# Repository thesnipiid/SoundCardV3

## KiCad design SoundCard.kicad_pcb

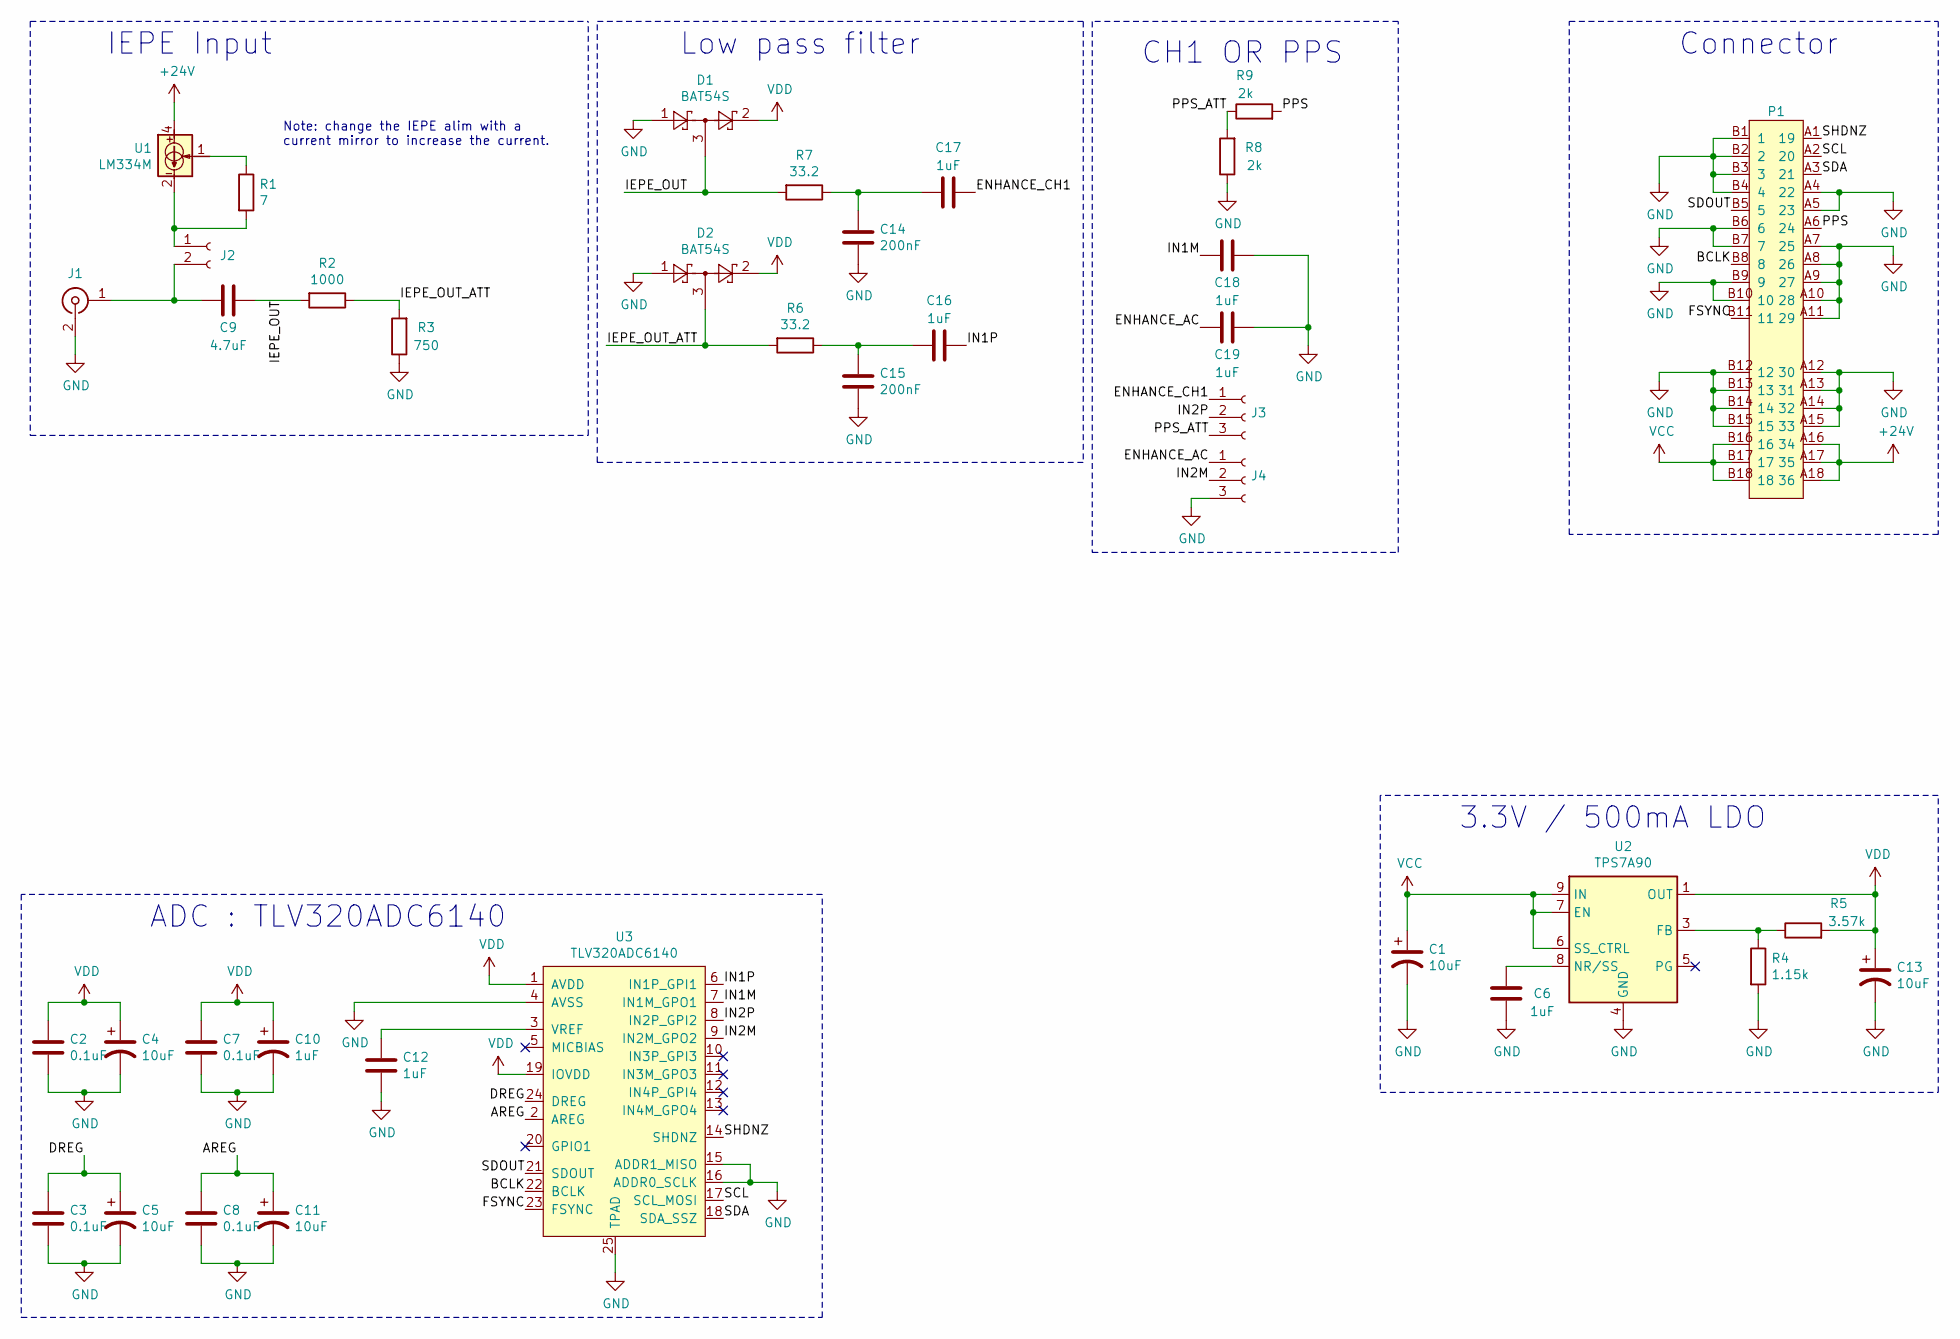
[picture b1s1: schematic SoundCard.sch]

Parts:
C1, C4, C5, C11, C13: 10uF; C_0805_2012Metric
C2, C3, C7, C8: 0.1uF; C_0402_1005Metric
C6, C12, C16, C17, C18, C19: 1uF; C_0402_1005Metric
C9: 4.7uF; C_0805_2012Metric
C10: 1uF; C_0805_2012Metric
C14, C15: 200nF; C_0402_1005Metric
D1, D2: BAT54S; SOT-23
J1: Conn_Coaxial_inv; SMA_Amphenol_901-144_Vertical
J2: Conn_01x02_Female; SolderJumper-2_P1.3mm_Bridged_Pad1.0x1.5mm
J3, J4: Conn_01x03_Female; SolderJumper-3_P1.3mm_Open_Pad1.0x1.5mm
P1: CONN_36_P1.00_PCI; BUS_PCIexpress_x1
R1: 7; R_0603_1608Metric
R2: 1000; R_0402_1005Metric
R3: 750; R_0402_1005Metric
R4: 1.15k; R_0402_1005Metric
R5: 3.57k; R_0402_1005Metric
R6, R7: 33.2; R_0402_1005Metric
R8, R9: 2k; R_0402_1005Metric
U1: LM334M; SOIC-8_3.9x4.9mm_P1.27mm
U2: TPS7A90; Texas_S-PDSO-N10_EP1.2x2mm
U3: TLV320ADC6140; Texas_S-PWQFN-N24_EP2.7x2.7mm_ThermalVias

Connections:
+24V: P1.A16 (34), P1.A17 (35), P1.A18 (36), U1.4
/AREG: C8.2, C11.1, U3.2 (AREG)
/BCLK: P1.B8 (8), U3.22 (BCLK)
/DREG: C3.2, C5.1, U3.24 (DREG)
/ENHANCE_AC: C19.1, J4.1
/ENHANCE_CH1: C17.2, J3.1
/FSYNC: P1.B11 (11), U3.23 (FSYNC)
/IEPE_OUT: C9.2, D1.3, R2.2, R7.2
/IEPE_OUT_ATT: D2.3, R2.1, R3.2, R6.2
/IN1M: C18.1, U3.7 (IN1M_GPO1)
/IN1P: C16.2, U3.6 (IN1P_GPI1)
/IN2M: J4.2, U3.9 (IN2M_GPO2)
/IN2P: J3.2, U3.8 (IN2P_GPI2)
/PPS: P1.A6 (24), R9.2
/PPS_ATT: J3.3, R8.2, R9.1
/SCL: P1.A2 (20), U3.17 (SCL_MOSI)
/SDA: P1.A3 (21), U3.18 (SDA_SSZ)
/SDOUT: P1.B5 (5), U3.21 (SDOUT)
/SHDNZ: P1.A1 (19), U3.14 (SHDNZ)
GND: C1.2, C2.1, C3.1, C4.2, C5.2, C6.1, C7.1, C8.1, C10.2, C11.2, C12.1, C13.2, C14.2, C15.2, C18.2, C19.2, D1.1, D2.1, J1.2 (In), J4.3, P1.A4 (22), P1.A5 (23), P1.A7 (25), P1.A8 (26), P1.A9 (27), P1.A10 (28), P1.A11 (29), P1.A12 (30), P1.A13 (31), P1.A14 (32), P1.A15 (33), P1.B1 (1), P1.B2 (2), P1.B3 (3), P1.B4 (4), P1.B6 (6), P1.B7 (7), P1.B9 (9), P1.B10 (10), P1.B12 (12), P1.B13 (13), P1.B14 (14), P1.B15 (15), R3.1, R4.2, R8.1, U2.4 (GND), U2.11 (GND), U3.4 (AVSS), U3.15 (ADDR1_MISO), U3.16 (ADDR0_SCLK), U3.25 (TPAD)
unnamed: C6.2, U2.8 (NR/SS)
unnamed: C9.1, J1.1 (Ext), J2.2
unnamed: C12.2, U3.3 (VREF)
unnamed: C14.1, C17.1, R7.1
unnamed: C15.1, C16.1, R6.1
unnamed: J2.1, R1.2, U1.2, U1.3, U1.6, U1.7
unnamed: R1.1, U1.1
unnamed: R4.1, R5.1, U2.3 (FB)
VCC: C1.1, P1.B16 (16), P1.B17 (17), P1.B18 (18), U2.6 (SS_CTRL), U2.7 (EN), U2.9 (IN), U2.10 (IN)
VDD: C2.2, C4.1, C7.2, C10.1, C13.1, D1.2, D2.2, R5.2, U2.1 (OUT), U2.2 (OUT), U3.1 (AVDD), U3.19 (IOVDD)

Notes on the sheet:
IEPE Input
Connector
ADC : TLV320ADC6140
CH1 OR PPS
3.3V / 500mA LDO
Low pass filter
Note: change the IEPE alim with a current mirror to increase the current.

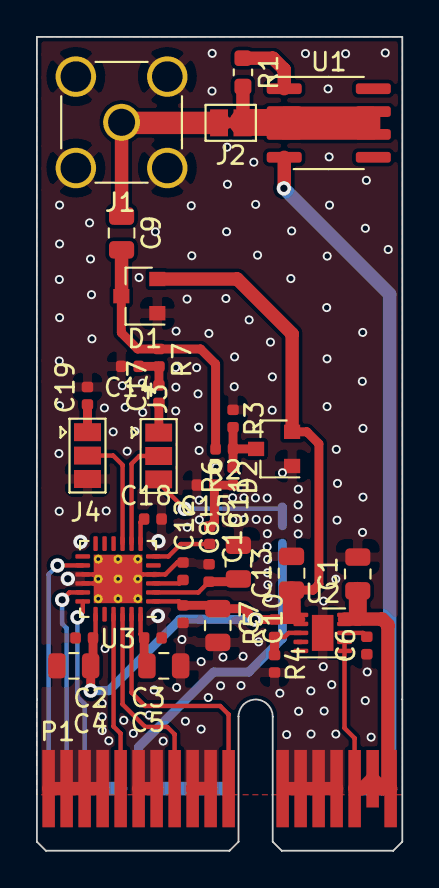
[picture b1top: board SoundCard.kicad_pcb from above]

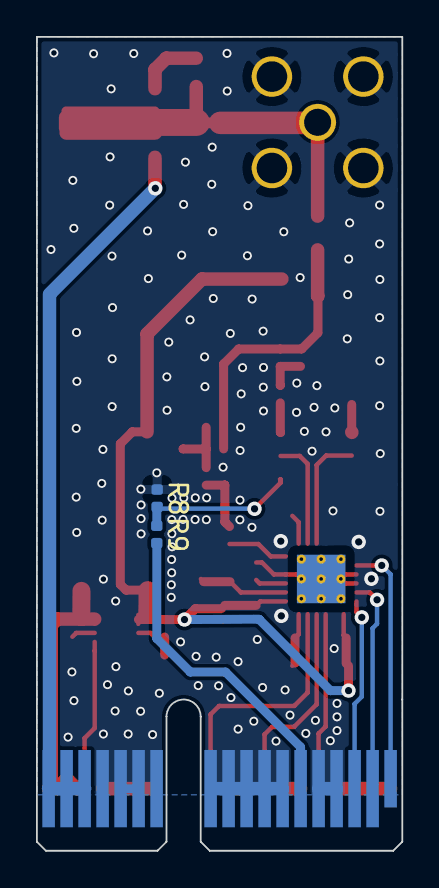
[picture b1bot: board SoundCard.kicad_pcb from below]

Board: 2 copper layers, 20.3 x 45.2 mm, 38 parts (2 on the bottom side), 30 nets.

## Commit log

2020-08-04 init
2020-08-05 Adding 1.65V LDO for Recommon voltage of AOP
2020-08-10 modif suite à test, simplification.
2020-08-11 routage terminé
2020-08-11 gerber generé
